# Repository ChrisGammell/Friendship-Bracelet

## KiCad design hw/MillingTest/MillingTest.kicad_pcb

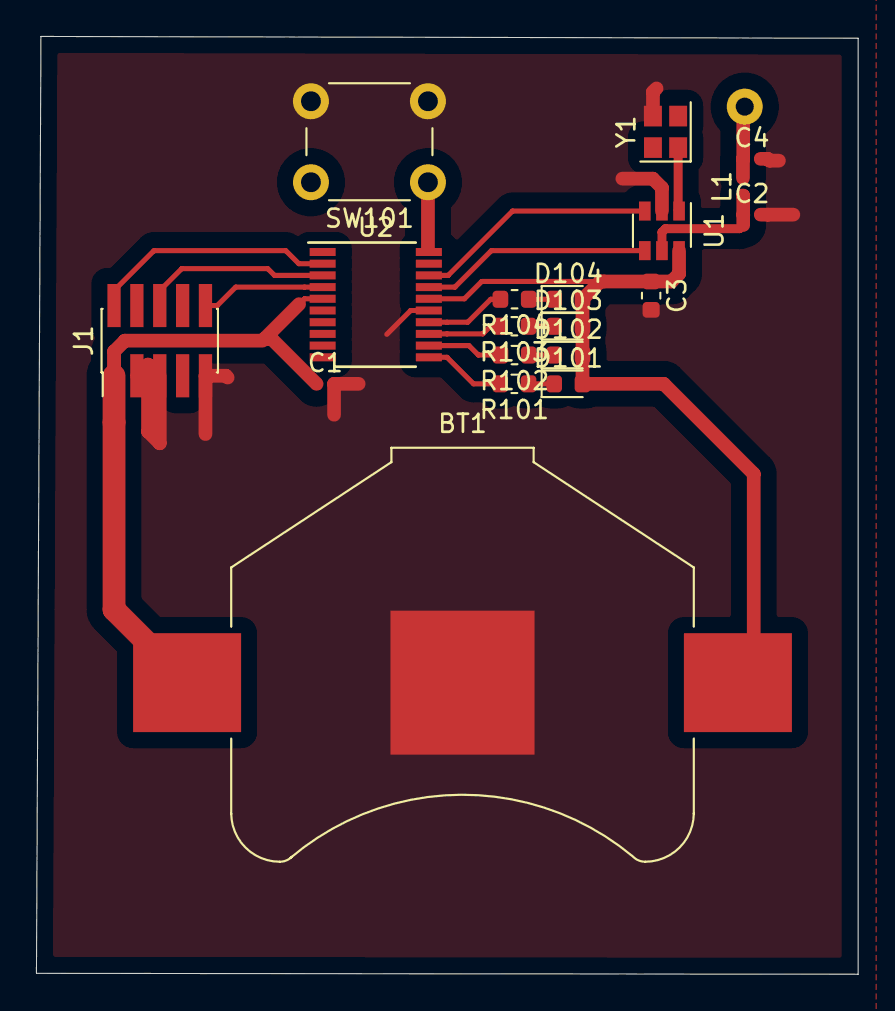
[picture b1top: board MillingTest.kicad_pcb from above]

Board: 2 copper layers, 45.7 x 52.1 mm, 20 parts (1 on the bottom side), 19 nets.

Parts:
AE1: Antenna; TestPoint_THTPad_D2.0mm_Drill1.0mm
BT1: Battery; BatteryHolder_Keystone_3008_1x2450
C1, C2, C4: C; C_0402_1005Metric
C3: C; C_0603_1608Metric
D101, D102, D103, D104: LED; LED_0603_1608Metric
J1: Conn_ARM_JTAG_SWD_10; PinHeader_2x05_P1.27mm_Vertical_SMD
L1: L; L_0402_1005Metric
R101, R102, R103, R104: R; R_0603_1608Metric
SW101: SW_Push; SW_PUSH_6mm
U1: CMT2110A; SOT-23-6
U2: STM32F030F4Px; TSSOP-20_4.4x6.5mm_P0.65mm
Y1: Crystal; Crystal_SMD_2520-4Pin_2.5x2.0mm

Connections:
/CLK: U1.4, U2.17
/DATA: U1.3, U2.18
/VBAT: BT1.1, C1.1, C3.1, D101.2, D102.2, D103.2, D104.2, J1.1, U1.6, U2.5, U2.16
GND: BT1.2, C1.2, C2.2, C3.2, C4.2, J1.3, J1.5, J1.9, SW101.2, U1.2, U2.15, Y1.3
unnamed: AE1.1, C4.1, L1.2
unnamed: C2.1, L1.1, U1.5
unnamed: D101.1, R101.1
unnamed: D102.1, R102.1
unnamed: D103.1, R103.1
unnamed: D104.1, R104.1
unnamed: J1.2, U2.2
unnamed: J1.6, U2.3
unnamed: J1.10, U2.4
unnamed: R101.2, U2.11
unnamed: R102.2, U2.12
unnamed: R103.2, U2.13
unnamed: R104.2, U2.14
unnamed: SW101.1, U2.20
unnamed: U1.1, Y1.1

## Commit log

2019-10-11 Spaces not allowed?
2019-10-11 Ah, they are, I just had 'em in the wrong place
2019-10-29 Added milling test board
2019-10-29 Finished layout with LEDs on board
2019-10-29 Moved over NucleoTest2 folder
2019-10-29 Removed NucleoTest2
2019-10-29 Moved files back in
